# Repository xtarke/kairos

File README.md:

# Projeto Kairos

## Tópicos

### Sensores

- temperatura0: RS485=0x0a
- temperatura1: RS485=0x0e
- temperatura2: RS485=0x0b
- temperatura3: RS485=0x0c
- pressão: 4 a 20mA

### Configuração

- tanque/xyz/cfg/0 : temperatura 0 ativado/desativado
- tanque/xyz/cfg/1 : temperatura 1 ativado/desativado
- tanque/xyz/cfg/2 : temperatura 2 ativado/desativado
- tanque/xyz/cfg/3 : temperatura 3 ativado/desativado
- tanque/xyz/cfg/4 : pressão ativado/desativado
- Configuração do fundo de escala do sensor de pressão:
    - tanque/xyz/cfg/5 : alpha (multiplicado por 1000).
    - tanque/xyz/cfg/6 : beta (multiplicado por 1000).

```
P(i) = alpha * i - beta

alpha = Full_Scale  * 1000
        ----------
           0.016

beta =  Full_Scale * 0.004       Full_Scale * 1000
        ------------------  =    -----------
            0.016                    4

P(i) = 375000*i - 1500   (0..6000 mBAR)
```

### Dados

- tanque/xyz/temperatura/0
- tanque/xyz/temperatura/1
- tanque/xyz/temperatura/2
- tanque/xyz/temperatura/3
- tanque/xyz/pressao

## Guia de instalação banco de dados temporal

- Instalar InfluxDB
- Instalar Grafana [GrafanaInstall](https://grafana.com/grafana/download?platform=arm)
- Instalar Python3 Influx: ```pip3 install influxdb --user```
- Instalar paho-mqtt: ```pip3 install paho-mqtt --user```

### Configurar InfluxDB

Maiores detalhes  em [InfluxManual](https://docs.influxdata.com/influxdb/v1.7/administration/authentication_and_authorization/#authorization)

- Criação usuário _admin_:
```
CREATE USER admin WITH PASSWORD '<password>' WITH ALL PRIVILEGES
```

- Influx desabilita usuários por padrão, portanto altere a configuração de _/etc/influxdb/influxdb.conf_ para:
```
[http]
  enabled = true
  bind-address = ":8086"
  auth-enabled = true #<--------------
  log-enabled = true
  write-tracing = false
  pprof-enabled = false
  https-enabled = true
  https-certificate = "/etc/ssl/influxdb.pem"
```

- Criação usuário _xyz_:
```
    CREATE USER xyz WITH PASSWORD '123456'
```

- Conexão a partir desse momento exige usuário e senha:

```
    influx -username admin -password <senha>
```

- Criação do banco de dados:

```
    CREATE DATABASE "myDB"
```

- Criação do banco de dados com duração de 1 dia e replicação igual a 1 [Database Mangement](https://docs.influxdata.com/influxdb/v1.7/query_language/database_management/):

```
     CREATE RETENTION POLICY "one_day_only" ON "myDB" DURATION 1d REPLICATION 1
```

- Permissão de escrita/leitura para o usuário:

```
    GRANT ALL ON "database_name" TO "username"
```

## Manutenção banco de dados:

```
show databases
use <database_name>
select * from camera_temp
drop series from camera_temp

select * from "temp20-1" where "Float_value" > 1000

#See: https://stackoverflow.com/questions/39685114/delete-points-with-unwanted-field-values-from-influxdb-measurement

# Copy all valid data to a temporary measurement
SELECT * INTO metrics_clean FROM metrics WHERE cpu!=-1

# Drop existing dirty measurement
DROP measurement metrics

# Copy temporary measurement to existing measurement
SELECT * INTO metrics FROM metrics_clean

With timerange

# Copy all valid data to a temporary measurement within timerange
SELECT * INTO metrics_clean FROM metrics WHERE cpu!=-1 and time > '<start_time>' and time '<end_time>';

# Delete existing dirty data within timerange
DELETE FROM metrics WHERE time > '<start_time>' and time '<end_time>';

# Copy temporary measurement to existing measurement
SELECT * INTO metrics FROM metrics_clean

```

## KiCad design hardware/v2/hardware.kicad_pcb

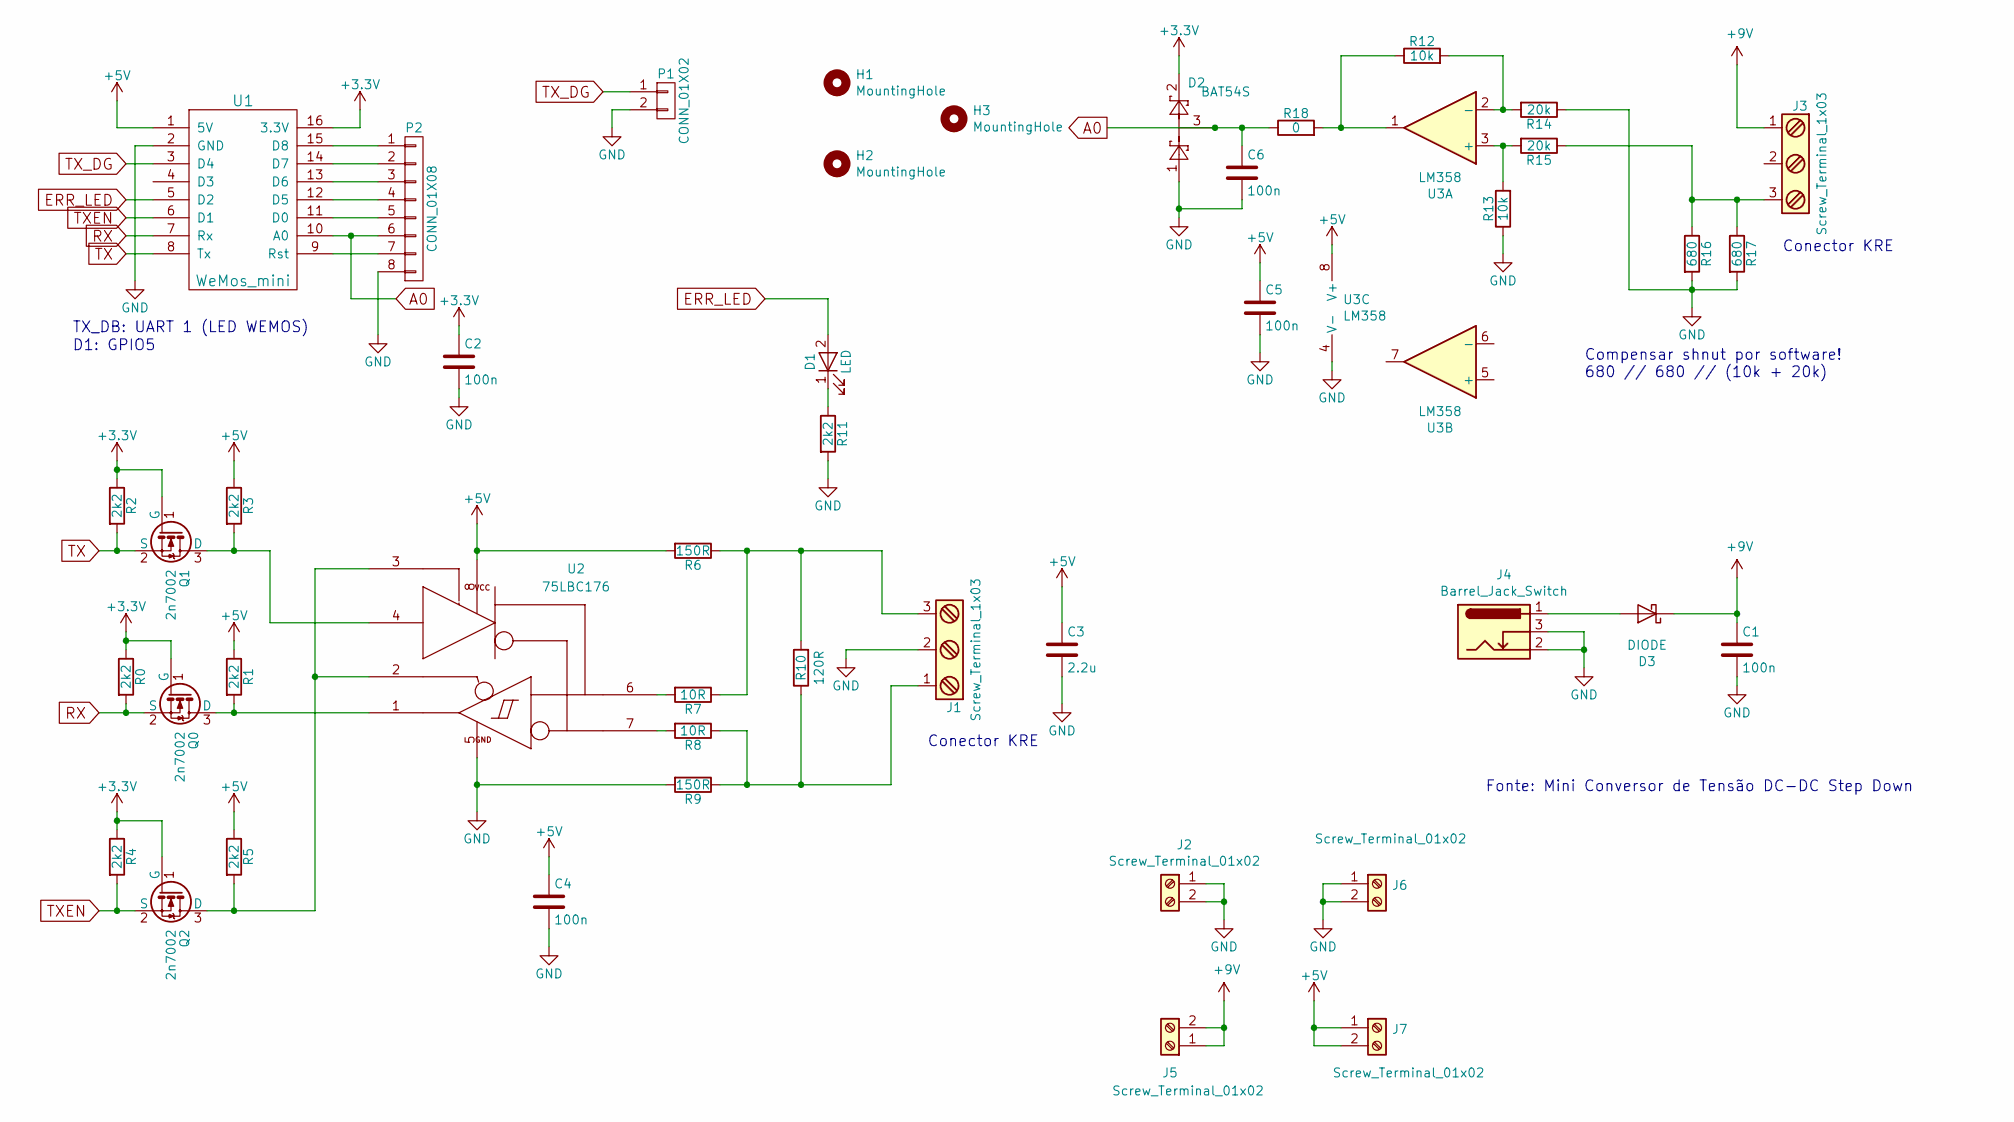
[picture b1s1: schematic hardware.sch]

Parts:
C1, C2, C4, C5, C6: 100n; C_0805_2012Metric_Pad1.15x1.40mm_HandSolder
C3: 2.2u; C_0805_2012Metric_Pad1.15x1.40mm_HandSolder
D1: LED; LED_D5.0mm
D2: BAT54S; SOT-23
D3: DIODE; D_SMB
H1, H2, H3: MountingHole; MountingHole_2.2mm_M2
J1, J3: Screw_Terminal_1x03; TerminalBlock_bornier-3_P5.08mm
J2, J5, J6, J7: Screw_Terminal_01x02; PinHeader_1x02_P2.54mm_Vertical
J4: Barrel_Jack_Switch; BarrelJack_Horizontal
P1: CONN_01X02; PinHeader_1x02_P2.54mm_Vertical
P2: CONN_01X08; PinHeader_1x08_P2.54mm_Vertical
Q0, Q1, Q2: 2n7002; SOT-23
R0, R1, R2, R3, R4, R5, R11: 2k2; R_0805_2012Metric_Pad1.15x1.40mm_HandSolder
R6, R9: 150R; R_Axial_DIN0207_L6.3mm_D2.5mm_P10.16mm_Horizontal
R7, R8: 10R; R_Axial_DIN0207_L6.3mm_D2.5mm_P10.16mm_Horizontal
R10: 120R; R_Axial_DIN0207_L6.3mm_D2.5mm_P10.16mm_Horizontal
R12, R13: 10k; R_1206_3216Metric_Pad1.42x1.75mm_HandSolder
R14, R15: 20k; R_1206_3216Metric_Pad1.42x1.75mm_HandSolder
R16, R17: 680; R_1206_3216Metric_Pad1.42x1.75mm_HandSolder
R18: 0; R_1206_3216Metric_Pad1.42x1.75mm_HandSolder
U1: WeMos_mini; D1_mini_board
U2: 75LBC176; DIP-8_W7.62mm
U3: LM358; SOIC-8_3.9x4.9mm_P1.27mm

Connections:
+3V3: C2.1, D2.2, Q0.1 (G), Q1.1 (G), Q2.1 (G), R0.1, R2.1, R4.1, U1.16 (3.3V)
+5V: C3.1, C4.1, C5.1, J7.1, J7.2, R1.1, R3.1, R5.1, R6.2, U1.1 (5V), U2.8 (VCC), U3.8 (V+)
+9V: C1.1, D3.1 (K), J3.1, J5.1, J5.2
A0: C6.1, D2.3, P2.6, R18.1, U1.10 (A0)
ERR_LED: D1.2 (A), U1.5 (D2)
GND: C1.2, C2.2, C3.2, C4.2, C5.2, C6.2, D2.1, J1.2, J2.1, J2.2, J4.2, J4.3, J6.1, J6.2, P1.2, P2.8, R9.2, R11.2, R13.1, R14.1, R16.2, R17.2, U1.2 (GND), U2.5 (GND), U3.4 (V-)
unnamed: D1.1 (K), R11.1
unnamed: D3.2 (A), J4.1
unnamed: J1.1, R8.1, R9.1, R10.1
unnamed: J1.3, R6.1, R7.1, R10.2
unnamed: J3.3, R15.1, R16.1, R17.1
unnamed: P2.1, U1.15 (D8)
unnamed: P2.2, U1.14 (D7)
unnamed: P2.3, U1.13 (D6)
unnamed: P2.4, U1.12 (D5)
unnamed: P2.5, U1.11 (D0)
unnamed: P2.7, U1.9 (Rst)
unnamed: Q0.3 (D), R1.2, U2.1 (ROUT)
unnamed: Q1.3 (D), R3.2, U2.4 (DIN)
unnamed: Q2.3 (D), R5.2, U2.2 (/RE), U2.3 (DE)
unnamed: R7.2, U2.6 (BUS+)
unnamed: R8.2, U2.7 (BUS-)
unnamed: R12.1, R18.2, U3.1
unnamed: R12.2, R14.2, U3.2 (-)
unnamed: R13.2, R15.2, U3.3 (+)
RX: Q0.2 (S), R0.2, U1.7 (Rx)
TX: Q1.2 (S), R2.2, U1.8 (Tx)
TXEN: Q2.2 (S), R4.2, U1.6 (D1)
TX_DG: P1.1, U1.3 (D4)

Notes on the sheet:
TX_DB: UART 1 (LED WEMOS)
D1: GPIO5
Fonte: Mini Conversor de Tensão DC-DC Step Down
Conector KRE
Compensar shnut por software! 680 // 680 // (10k + 20k)

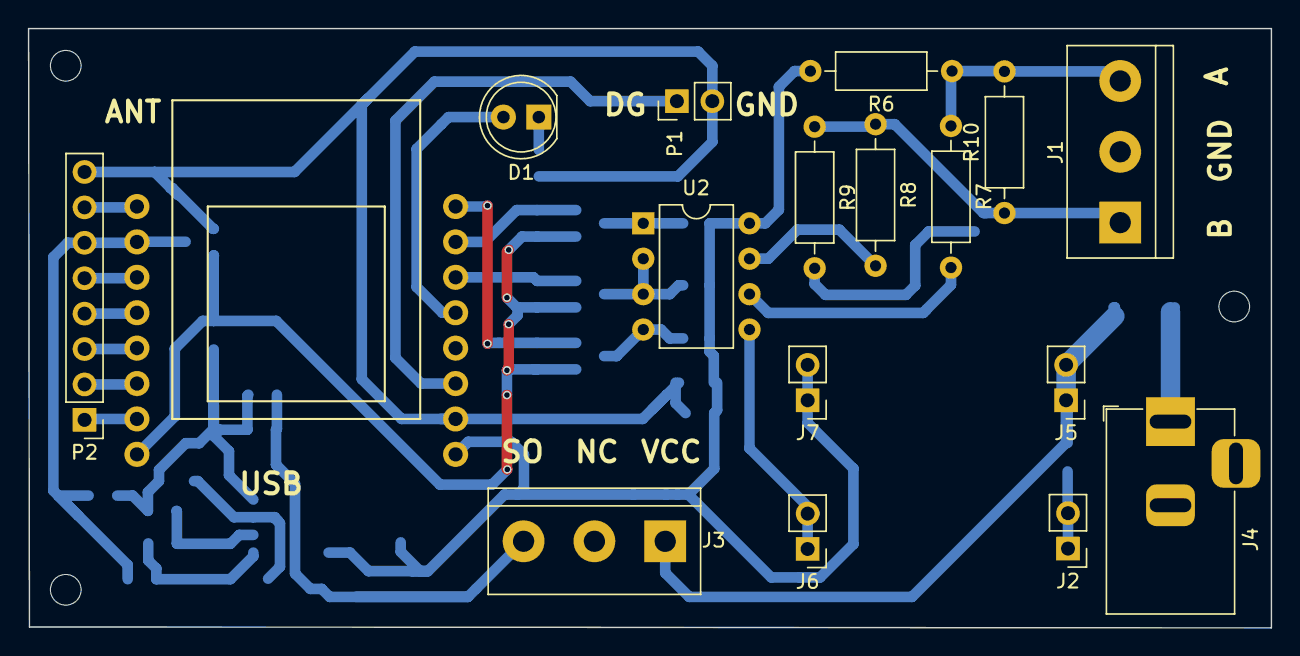
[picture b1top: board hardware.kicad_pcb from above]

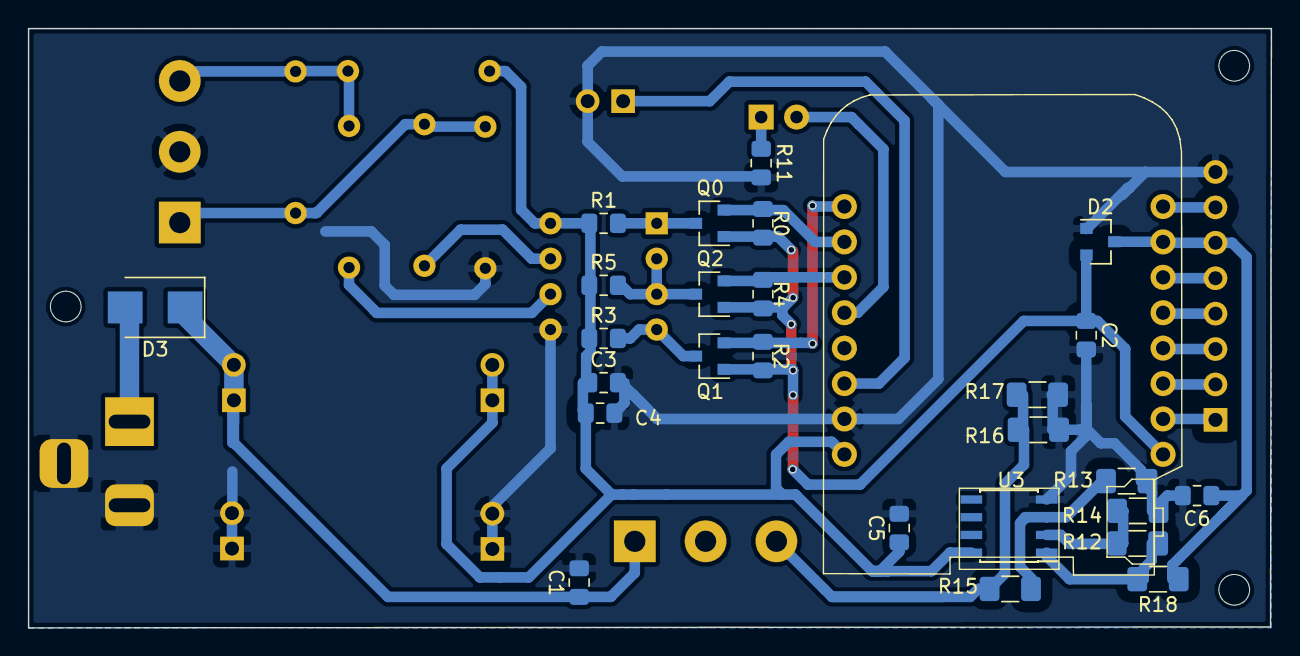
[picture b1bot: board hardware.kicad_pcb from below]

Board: 2 copper layers, 89.2 x 43.0 mm, 46 parts (27 on the bottom side), 29 nets.

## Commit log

2018-08-02 Added python sniffers
2018-08-15 Added esp firmware
2018-08-16 Mqtt publish test
2018-08-24 Added wificfg files
2018-08-30 Added queue structure
2018-09-04 Addec crc example and command task syncronization
2018-09-06 Added application status structure and sync semaphores.
2018-09-06 Implemented configuration messages
2018-09-06 Added python code
2018-10-09 Added hardware design
2018-12-06 Added mqtt WiFi guard; Code cleanup
2018-12-19 Testing conversion
2019-02-14 Added timestamp check
2019-02-21 Added systemd service
2019-02-27 Added support for 4 G101 controllers and publish 485 comm. errors.
2019-02-28 Added more measurements in python gateway
2019-03-01 Corrected python gateway
2019-03-08 Corrected error when broker disconnects. Corrected negative temperature.
2019-03-26 Added files
2019-03-27 PCB V2
2019-03-28 PCB V2
    barrel JAC colocado mais proximo da borda
2019-04-05 Added pressure sensor
2019-04-08 Added code for publish pressure information
2019-04-16 V3 hardware
2019-04-23 Corrected offset and display pressure in kgfm/cm2
2019-05-07 Added readme
2019-05-21 Board texts
2019-06-07 Added Wifi guards
2019-06-07 Added author comment
2019-06-10 Improved communication: TX_en is sometimes desync
2019-06-11 Implemented handler for 485 com. error
2019-08-02 Added more broker settings to wificfg
2019-08-07 Added dafault sta wifi and password
2019-08-08 Topic renamed
2019-08-08 Implemented gateway in raspiberry
2019-08-10 Added debug info in MQTT function
2019-09-03 Added configuration to enable/disable sensors
2019-09-05 Added full scale
2019-09-06 Scale of pressure sensor is now configurable
2019-09-06 Adjusted README
2020-02-07 Porting aplication to official espressif SDK
2020-02-10 Ported MQTT e RS485
2020-02-11 Application ported
2020-02-12 Added serial config
2020-02-13 Added kconfig
2020-02-13 Corrected indentation
2020-05-18 Try to connect forever
2020-05-18 Removed sdkconfig
2020-05-18 Removed sdkconfig.old
2020-07-02 Corrected config bug. Added conf from MQTT
2020-07-03 Reset wifi from network
2020-08-04 Added influxdb queries
2022-02-24 Adicionado TLS (mudar apenas url para mqtts://. Tempos de aquisição em 20s
2022-03-07 Added hivemqtt
